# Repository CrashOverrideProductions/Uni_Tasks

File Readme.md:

# Bachelor of Cyber Security

<!-- Repo Stats -->

<!-- Languages Card ?-->

## Course overview
<p align="justify">
Deakin’s Bachelor of Cyber Security provides a solid foundation of the cyber security literacy and technical skills required by industry for a cyber security professional including those allowing you to be able to investigate and combat cyber-crime and cyber terrorism. The digital world is central to the way we live, work, communicate and conduct business. Now more than ever, it’s vital that the data and systems providing these services be safeguarded by ethical professionals with strong cyber security literacy and technical skills.
<br><br>
Whether it’s keeping in touch with friends on social networks, paying bills online, or using water or electricity, we depend on secure networked systems to keep our confidential information safe and rely on the assurance provided by custodians of this information to carry out activities in our day-to-day lives. Governments, military, financial institutions, hospitals and other businesses are all facing an unprecedented sophistication of cyber-attacks and there is a shortage of people with the skills and capability needed to ensure security in cyberspace.
<br><br>
This course will teach you how to identify, diagnose, analyse and manage the challenges of Cyber security. You’ll cover areas such as computer crime and digital forensics, evaluating software for security vulnerabilities, designing secure databases, securing operating systems, assessing and reinforcing the security of websites, integrating security requirements into new developments, designing secure network architectures, performing risk assessments and responding to cyber security incidents.
<br><br<>
Classes use specialised software to enable practice of real world cyber-attack and response scenarios. You’ll consequently get the chance to reflect on the need for cyber security in a working environment, and the various solutions that might apply. The degree focuses on technical elements and sets you up with strong skills in critical thinking and problem solving. You’ll be able to apply your learning in the workplace, and capably deal with imminent threats and challenges from the digital space where interconnected vehicles, drones, smart home gadgets, mobile and wearable devices, and health-kits prosper.
<br><br>
The course will help you develop strong interpersonal skills and a capacity for team-work. You’ll also build your written and oral communications skills, which means that you’ll graduate as a qualified and highly employable IT professional. Career options include work as a security analyst, project manager, security system manager, cryptographer, business analyst, consultant, security system developer or programmer, information security auditor, law enforcement personnel or IT security engineer. An honours year is available for high-achieving students upon completion of this degree.
<br><br>
As a graduate of this degree you’ll be eligible for professional recognition with the Australian Computer Society (ACS) – Australia’s leading professional association for the Information and Communication Technology (ICT) sector. As a member, you’ll receive international recognition for your skills as well as professional development opportunities, networking and information resources.Units in the course may include assessment hurdle requirements
</p>

---

## Course Progression
| Unit Code | Unit Name                                              | Type     | Status  | Mark       |
|:---------:|--------------------------------------------------------|---------:|:-------:|-----------:|
|  SIT124   | Exploring IT                                           | CORE     | &check; | RPL        |
|  SIT105   | Thinking Technology and Design                         | CORE     | &check; | RPL        |
|  SIT182   | Real World Practices for Cyber Security                | CORE     | &check; | PASS       |
|           | UNIT OF STUDY FROM A FIRST YEAR UNDERGRADUATE PROGRAM  | ELECTIVE | &check; | RPL        |
|  SIT103   | Data and Information Managment                         | CORE     | &check; | RPL        |
|  SIT102   | Introduction to Programming                            | CORE     | &check; | RPL        |
|  SIT123   | Data Capture Technologies                              | ELECTIVE | &check; | CREDIT     |
|           | UNIT OF STUDY FROM A FIRST YEAR UNDERGRADUATE PROGRAM  | ELECTIVE | &check; | RPL        |
|  SIT223   | Professional Practice in a Digital World               | CORE     | &cross; |            |
|  SIT192   | Discrete Mathmatics                                    | CORE     | &check; | PASS       |
|  SIT232   | Object Oriented Development                            | ELECTIVE | &check; | CREDIT     |
|           | UNIT OF STUDY FROM A SECOND YEAR UNDERGRADUATE PROGRAM | ELECTIVE | &check; | RPL        |
|  SIT210   | Networks and Communications                            | CORE     | &check; | PASS       |
|  SIT282   | Computer Crime and Digital Forensics                   | CORE     | &check; | PASS       |
|  SIT284   | Cyber Security Managment                               | CORE     | &check; | PASS       |
|  SIT281   | Cryptography                                           | CORE     | &cross; |            |
|  SIT384   | Data Analytics for Cyber Security                      | CORE     | &check; | DISTINCTION|
|  SIT379   | Ethical Hacking                                        | CORE     | &check; | CREDIT     |
|  SIT 374  | Project Design                                         | CORE     | &cross; |            |
|  SIT382   | System Security                                        | CORE     | &cross; |            |
|  SIT306   | IT Placement                                           | CORE     | &cross; |            |
|  SIT302   | Project Delivery                                       | CORE     | &cross; |            |
|  SIT210   | Embedded Systems Development                           | ELECTIVE | &check; | CREDIT     |
|           | Elective TBD                                           | ELECTIVE | &cross; |            |
|           |                                                        |          |         |            |
|           |                                                        |Total Completed |   | 17/24      |
---

## Course rules
To complete the Bachelor of Cyber Security, students must attain 24 credit points. Most units (think of units as ‘subjects’) are equal to 1 credit point. So that means in order to gain 24 credit points, you’ll need to study 24 units (AKA ‘subjects’) over your entire degree. Most students choose to study 4 units per trimester, and usually undertake two trimesters each year.

The course comprises a total of 24 credit points, which must include the following:
+ 17 core units 
+ 7 elective units
+ Completion of STP050 Academic Integrity (0-credit-point compulsory unit)
+ Completion of SIT010 Safety Induction Program (0-credit-point compulsory unit)
+ Completion of STP010 Introduction to Work Placements (0-credit-point compulsory unit) 
+ Level 1 – maximum of 10 credit points
+ Levels 2 and 3 – minimum of 14 credit points over both levels
+ Level 3 – minimum of 6 credit points of which at least 4 must be SIT Course Grouped unitsStudents are required to meet the University’s academic progress and conduct requirements. Visit Deakin’s website for more information

---

## Course Particulars
|||
|------------------------------------------------------:|---------------------------------------------------------------------------------------------------------|
| Year                                                  | 2018 course information                                                                                 |
| Award granted                                         | Bachelor of Cyber Security                                                                              |
| Course Map                                            | deakin.edu.au/students/enrolment-fees-and-money/enrolments/course-maps                                  | 
| Campus                                                | Offered at Burwood (Melbourne), Waurn Ponds (Geelong)                                                   |
| Cloud Campus                                          | Yes                                                                                                     |
| Duration                                              | 3 years full-time or part-time equivalent                                                               |
| CRICOS course code                                    | 091336M                                                                                                 |
| Deakin course code                                    | S334 (version 4)                                                                                        |
| Approval status                                       | This course is approved by the University under the Higher Education Standards Framework                | 
| Australian Qualifications Framework (AQF) recognition | The award conferred upon completion is recognised in the Australian Qualifications Framework at Level 7 |

---

## Licencing 
<p align="justify">
© Justin Bland & Deakin University; 2021
<br><br>
Except as permitted by the copyright law applicable to you, you may not reproduce or communicate any of the content on this website, including files downloadable from this website, without the permission of the copyright owner.
<br><br>
The Australian Copyright Act allows certain uses of content from the internet without the copyright owner’s permission. This includes uses by educational institutions and by Commonwealth and State governments, provided fair compensation is paid. For more information, see www.copyright.com.au and www.copyright.org.au.
<br><br>
The owners of copyright in the content on this website may receive compensation for the use of their content by educational institutions and governments, including from licensing schemes managed by Copyright Agency.
<br><br>
We may change these terms of use from time to time. Check before re-using any content from this website.
</p>

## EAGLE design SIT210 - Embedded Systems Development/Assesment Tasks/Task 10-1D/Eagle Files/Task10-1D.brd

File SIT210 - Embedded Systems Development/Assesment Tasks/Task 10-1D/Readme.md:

# SIT210 Task 10.1D  

### **Project**: Terrarium Thermostat 

<!-- Repo Cover Image -->

<!-- Repo Intro -->
### Task Objective
Objective of this task is to understand, trial, and design a Printed Circuit Board (PCB). PCBs are important components in prototyping and delivery of any electrical system.
For this task, you will need to design a PCB for your project (please note that you do not need to print the designs for this task, just the design). Your design should consider the following:
1. Your PCB does not need to include the SoC you are using (although some PCB design tools allow you to include chips like ATmega on your design). You can design your PC as a board to be used on the side, or as a shield/hat for your main device depending on which mark you are targeting (see below requirement for D/HD).
2. Your PCB should include all wiring, resistors, LEDs, sensors (either on the PCB itself, or with dedicated location/pins to soldier sensors on your PCB). If you are not designing a shield/hat, have interfaces for wiring from your main device to the PCB and clearly mark them on the PCB.

D: If you are targeting Distinction, your PCB could be in any form you wish. You can either make the board fit an enclosure/box of your liking.

~~HD: If you are targeting High Distinction, your PCB needs to take the form of a Shield for either a 40 pin Raspberry Pi (if using in your project, or designing PCB for 7.3D), or follow Feather standard (to be used with particle Argon.~~

#### Task Submission Details
You are required to submit two files for this task:
1. Create a Repository on Github and name it SIT210_PCB_Files and Put your design files/project on Github and a share the link to that repository on a document and submit on OnTrack
2. Provide a screenshot of the PCB you have developed.
Please note that unless you personally want that PCB, this task does not require your to have your design printed on an actual board.

---
<!-- Files -->
#### Files
|File     |Type|Link                                                                                                                                                                                                 | 
|---------|:--:|:---------------------------------------------------------------------------------------------------------------------------------------------------------------------------------------------------:|
|Schematic|.PDF|<a href="https://github.com/CrashOverrideProductions/ProfessionalDevelopment/blob/main/Uni%20Files/SIT210%20-%20Embedded%20Systems%20Development/Task%2010-1D/Schematic.pdf">This Directory</a>      |
|---------|----|------------------|
|Schematic|.SCH|<a href="https://github.com/CrashOverrideProductions/ProfessionalDevelopment/blob/main/Uni%20Files/SIT210%20-%20Embedded%20Systems%20Development/Task%2010-1D/Eagle%20Files/Task10-1D.sch">/Eagle</a>|
|Board    |.BRD|<a href="https://github.com/CrashOverrideProductions/ProfessionalDevelopment/blob/main/Uni%20Files/SIT210%20-%20Embedded%20Systems%20Development/Task%2010-1D/Eagle%20Files/Task10-1D.brd">/Eagle</a>|
|---------|----|------------------|
|Gerber   | N/A|<a href="https://github.com/CrashOverrideProductions/ProfessionalDevelopment/tree/main/Uni%20Files/SIT210%20-%20Embedded%20Systems%20Development/Task%2010-1D/Gerber">/Gerber</a>                    |
|---------|----|------------------|
|Renders  | N/A|<a href="https://github.com/CrashOverrideProductions/ProfessionalDevelopment/tree/main/Uni%20Files/SIT210%20-%20Embedded%20Systems%20Development/Task%2010-1D/Renders">/Renders</a>                  |

<!-- Licencing Always at the Bottom -->
---
### Licencing 

**Creative Commons: Attribution - NonCommercial - ShareAlike 4.0 International (CC BY-NC-SA 4.0)**

**You are free to:**
**Share** — copy and redistribute the material in any medium or format
**Adapt** — remix, transform, and build upon the material

**Under the following terms:**
**Attribution** — You must give appropriate credit, provide a link to the license, and indicate if changes were made. You may do so in any reasonable manner, but not in any way that suggests the licensor endorses you or your use.

**NonCommercial** — You may not use the material for commercial purposes.

**ShareAlike** — If you remix, transform, or build upon the material, you must distribute your contributions under the same license as the original.

No additional restrictions — You may not apply legal terms or technological measures that legally restrict others from doing anything the license permits.

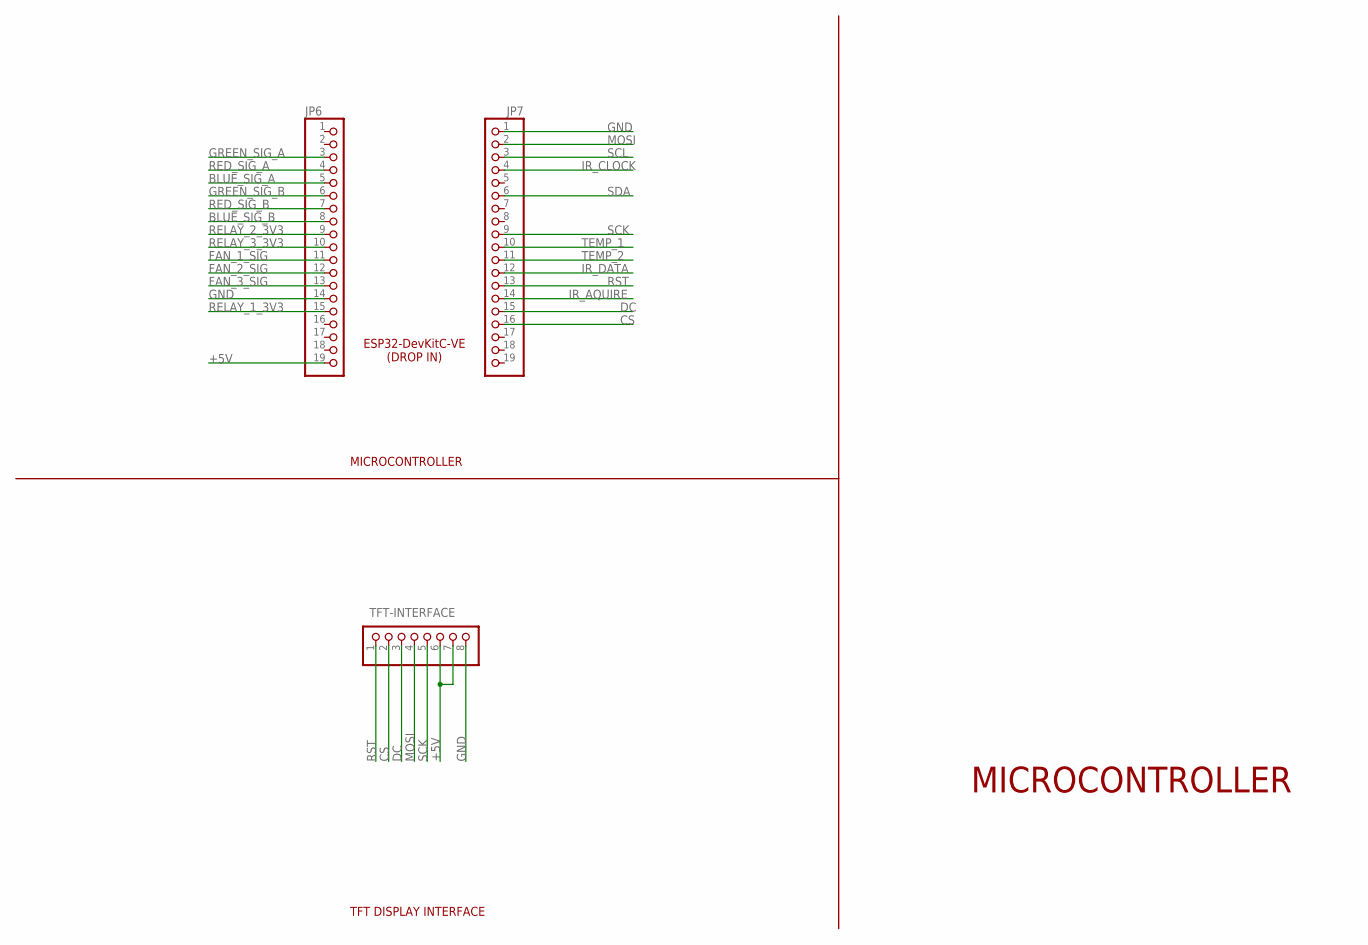
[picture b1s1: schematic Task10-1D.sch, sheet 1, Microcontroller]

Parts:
JP6, JP7: PINHD-1X19; 1X19
TFT-INTERFACE: PINHD-1X8; 1X08

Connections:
+5V: JP6.19, TFT-INTERFACE.6, TFT-INTERFACE.7; also elsewhere on the board
BLUE_SIG_A: JP6.5; also elsewhere on the board
BLUE_SIG_B: JP6.8; also elsewhere on the board
CS: JP7.16, TFT-INTERFACE.2
DC: JP7.15, TFT-INTERFACE.3
FAN_1_SIG: JP6.11; also elsewhere on the board
FAN_2_SIG: JP6.12; also elsewhere on the board
FAN_3_SIG: JP6.13; also elsewhere on the board
GND: JP6.14, JP7.1, TFT-INTERFACE.8; also elsewhere on the board
GREEN_SIG_A: JP6.3; also elsewhere on the board
GREEN_SIG_B: JP6.6; also elsewhere on the board
IR_AQUIRE: JP7.14; also elsewhere on the board
IR_CLOCK: JP7.4; also elsewhere on the board
IR_DATA: JP7.12; also elsewhere on the board
MOSI: JP7.2, TFT-INTERFACE.4
RED_SIG_A: JP6.4; also elsewhere on the board
RED_SIG_B: JP6.7; also elsewhere on the board
RELAY_1_3V3: JP6.15; also elsewhere on the board
RELAY_2_3V3: JP6.9; also elsewhere on the board
RELAY_3_3V3: JP6.10; also elsewhere on the board
RST: JP7.13, TFT-INTERFACE.1
SCK: JP7.9, TFT-INTERFACE.5
SCL: JP7.3; also elsewhere on the board
SDA: JP7.6; also elsewhere on the board
TEMP_1: JP7.10; also elsewhere on the board
TEMP_2: JP7.11; also elsewhere on the board

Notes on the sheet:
ESP32-DevKitC-VE (DROP IN)
MICROCONTROLLER
TFT DISPLAY INTERFACE

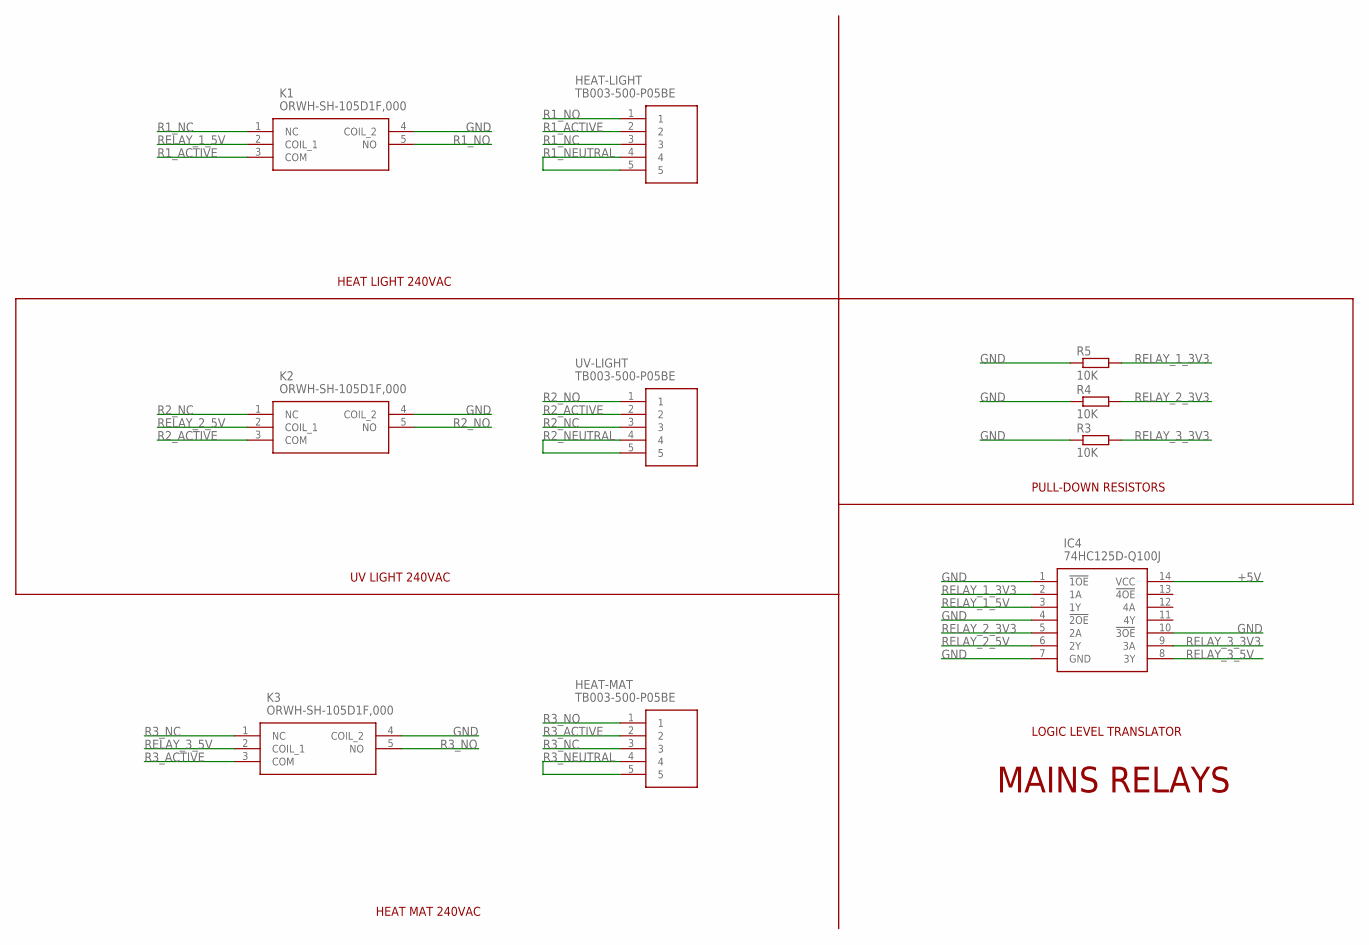
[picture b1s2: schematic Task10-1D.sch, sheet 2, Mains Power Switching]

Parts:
HEAT-LIGHT: TB003-500-P05BE; TB003500P05BE
HEAT-MAT: TB003-500-P05BE; TB003500P05BE
IC4: 74HC125D-Q100J; SOIC127P600X175-14N
K1, K2, K3: ORWH-SH-105D1F,000; ORWH-1T
R3, R4, R5: 10K; M0805
UV-LIGHT: TB003-500-P05BE; TB003500P05BE

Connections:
+5V: IC4.14 (VCC); also elsewhere on the board
GND: IC4.1 (!1OE), IC4.4 (!2OE), IC4.7 (GND), IC4.10 (!3OE), K1.4 (COIL_2), K2.4 (COIL_2), K3.4 (COIL_2), R3.1, R4.1, R5.1; also elsewhere on the board
R1_ACTIVE: HEAT-LIGHT.2, K1.3 (COM)
R1_NC: HEAT-LIGHT.3, K1.1 (NC)
R1_NEUTRAL: HEAT-LIGHT.4, HEAT-LIGHT.5
R1_NO: HEAT-LIGHT.1, K1.5 (NO)
R2_ACTIVE: K2.3 (COM), UV-LIGHT.2
R2_NC: K2.1 (NC), UV-LIGHT.3
R2_NEUTRAL: UV-LIGHT.4, UV-LIGHT.5
R2_NO: K2.5 (NO), UV-LIGHT.1
R3_ACTIVE: HEAT-MAT.2, K3.3 (COM)
R3_NC: HEAT-MAT.3, K3.1 (NC)
R3_NEUTRAL: HEAT-MAT.4, HEAT-MAT.5
R3_NO: HEAT-MAT.1, K3.5 (NO)
RELAY_1_3V3: IC4.2 (1A), R5.2; also elsewhere on the board
RELAY_1_5V: IC4.3 (1Y), K1.2 (COIL_1)
RELAY_2_3V3: IC4.5 (2A), R4.2; also elsewhere on the board
RELAY_2_5V: IC4.6 (2Y), K2.2 (COIL_1)
RELAY_3_3V3: IC4.9 (3A), R3.2; also elsewhere on the board
RELAY_3_5V: IC4.8 (3Y), K3.2 (COIL_1)

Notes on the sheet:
MAINS RELAYS
HEAT MAT 240VAC
UV LIGHT 240VAC
HEAT LIGHT 240VAC
LOGIC LEVEL TRANSLATOR
PULL-DOWN RESISTORS

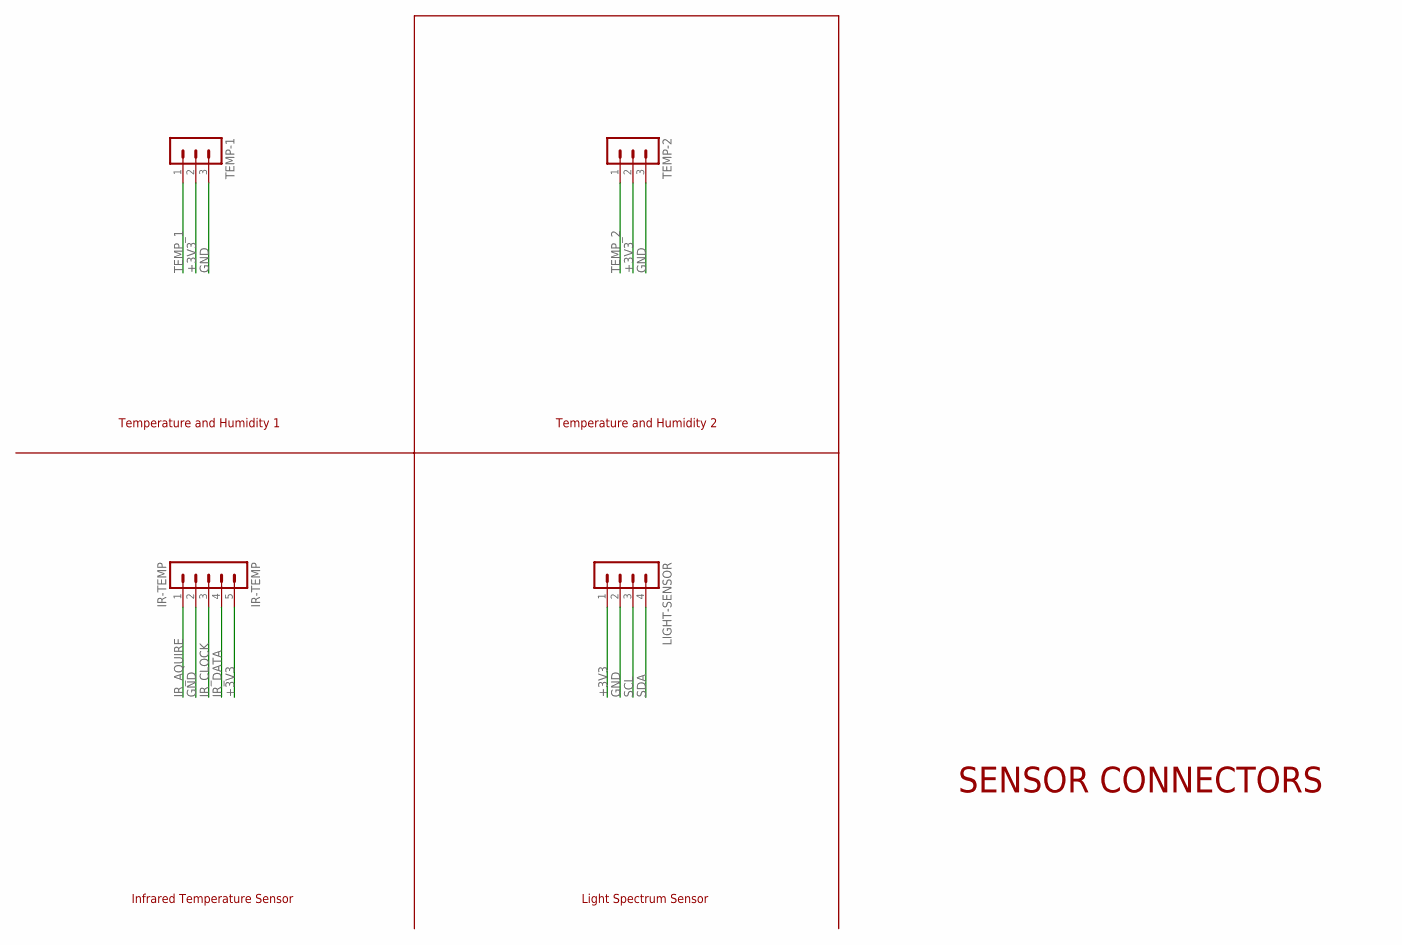
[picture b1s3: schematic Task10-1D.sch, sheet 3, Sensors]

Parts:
IR-TEMP: IR-TEMP; MA05-1
LIGHT-SENSOR: MA04-1
TEMP-1, TEMP-2: MA03-1

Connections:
+3V3: IR-TEMP.5, LIGHT-SENSOR.1, TEMP-1.2, TEMP-2.2; also elsewhere on the board
GND: IR-TEMP.2, LIGHT-SENSOR.2, TEMP-1.3, TEMP-2.3; also elsewhere on the board
IR_AQUIRE: IR-TEMP.1; also elsewhere on the board
IR_CLOCK: IR-TEMP.3; also elsewhere on the board
IR_DATA: IR-TEMP.4; also elsewhere on the board
SCL: LIGHT-SENSOR.3; also elsewhere on the board
SDA: LIGHT-SENSOR.4; also elsewhere on the board
TEMP_1: TEMP-1.1; also elsewhere on the board
TEMP_2: TEMP-2.1; also elsewhere on the board

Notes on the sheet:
Temperature and Humidity 1
Temperature and Humidity 2
Infrared Temperature Sensor
Light Spectrum Sensor
SENSOR CONNECTORS

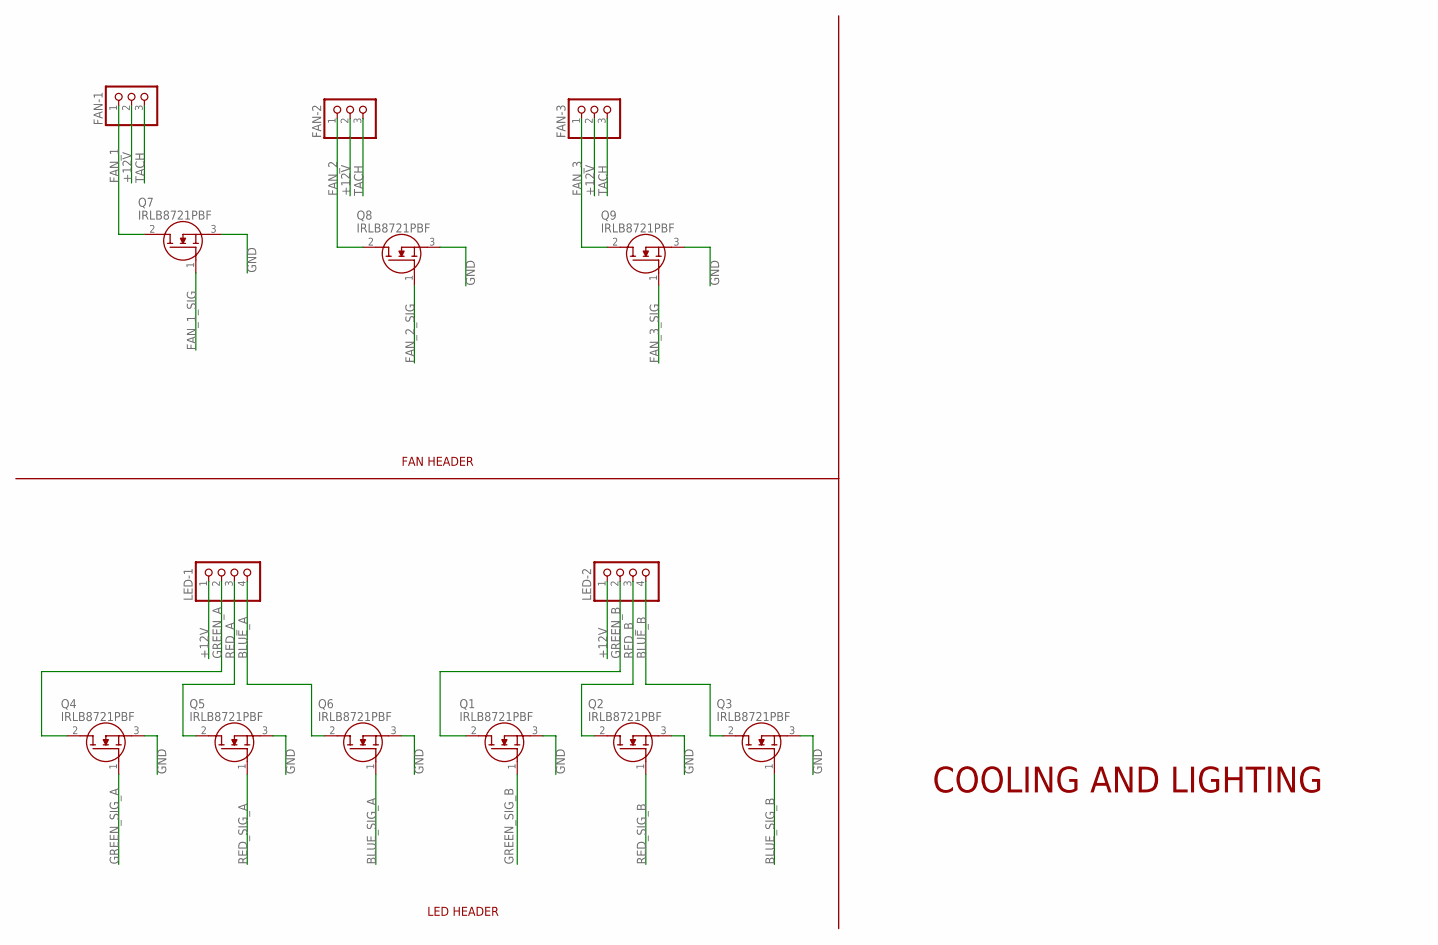
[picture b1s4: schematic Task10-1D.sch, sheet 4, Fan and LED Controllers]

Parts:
FAN-1, FAN-2, FAN-3: PINHD-1X3; 1X03
LED-1, LED-2: PINHD-1X4; 1X04
Q1, Q2, Q3, Q4, Q5, Q6, Q7, Q8, Q9: IRLB8721PBF; TO254P483X1016X1994-3P

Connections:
+12V: FAN-1.2, FAN-2.2, FAN-3.2, LED-1.1, LED-2.1; also elsewhere on the board
BLUE_A: LED-1.4, Q6.2 (D)
BLUE_B: LED-2.4, Q3.2 (D)
BLUE_SIG_A: Q6.1 (G); also elsewhere on the board
BLUE_SIG_B: Q3.1 (G); also elsewhere on the board
FAN_1: FAN-1.1, Q7.2 (D)
FAN_1_SIG: Q7.1 (G); also elsewhere on the board
FAN_2: FAN-2.1, Q8.2 (D)
FAN_2_SIG: Q8.1 (G); also elsewhere on the board
FAN_3: FAN-3.1, Q9.2 (D)
FAN_3_SIG: Q9.1 (G); also elsewhere on the board
GND: Q1.3 (S), Q2.3 (S), Q3.3 (S), Q4.3 (S), Q5.3 (S), Q6.3 (S), Q7.3 (S), Q8.3 (S), Q9.3 (S); also elsewhere on the board
GREEN_A: LED-1.2, Q4.2 (D)
GREEN_B: LED-2.2, Q1.2 (D)
GREEN_SIG_A: Q4.1 (G); also elsewhere on the board
GREEN_SIG_B: Q1.1 (G); also elsewhere on the board
RED_A: LED-1.3, Q5.2 (D)
RED_B: LED-2.3, Q2.2 (D)
RED_SIG_A: Q5.1 (G); also elsewhere on the board
RED_SIG_B: Q2.1 (G); also elsewhere on the board
TACH: FAN-1.3, FAN-2.3, FAN-3.3

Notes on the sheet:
LED HEADER
FAN HEADER
COOLING AND LIGHTING

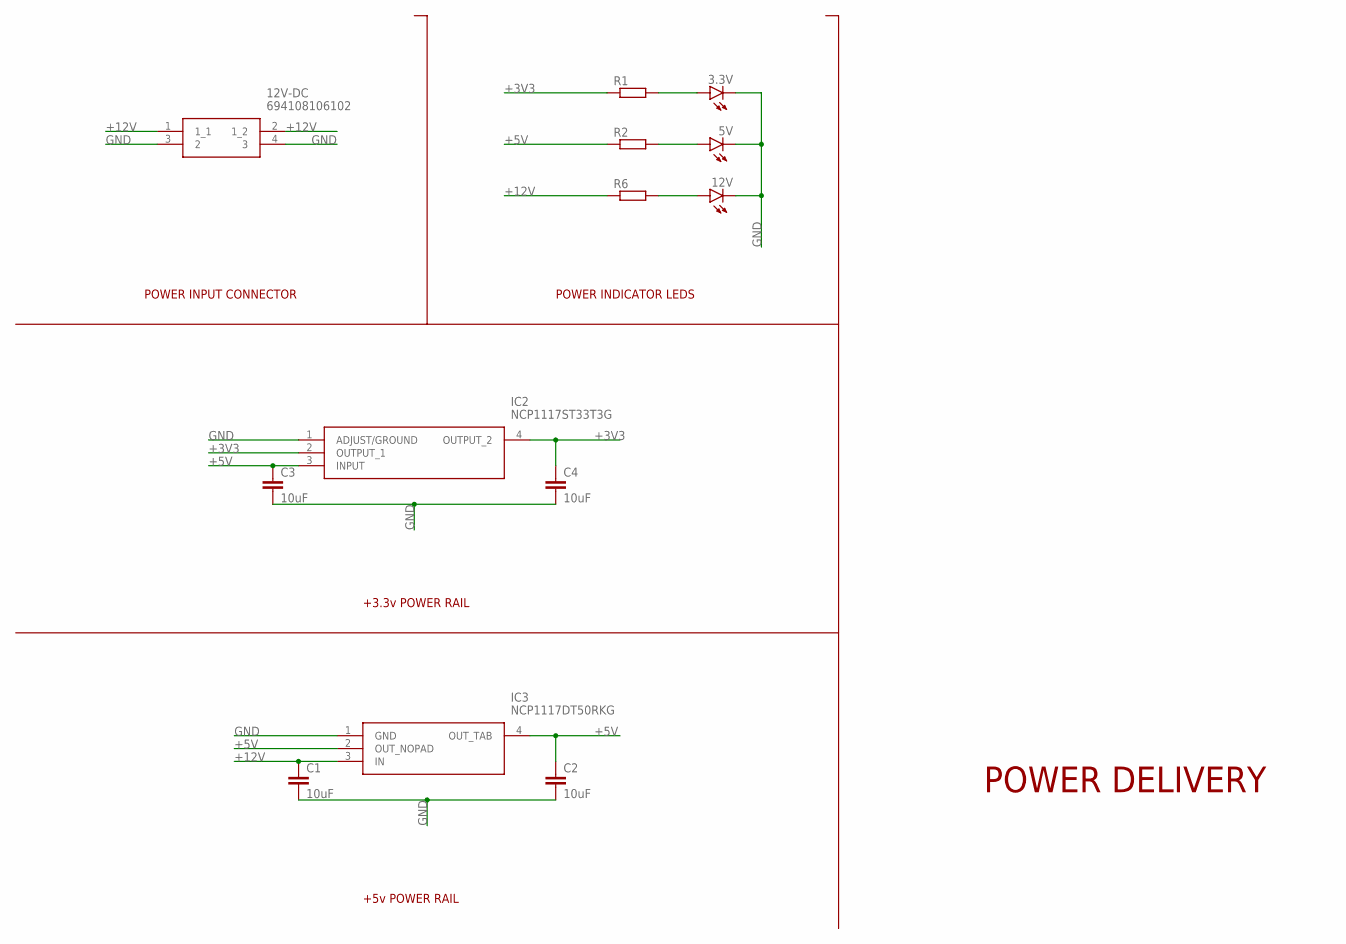
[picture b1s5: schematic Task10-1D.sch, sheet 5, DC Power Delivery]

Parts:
3.3V, 5V, 12V: LEDCHIP-LED0805; CHIP-LED0805
12V-DC: 694108106102
C1, C2, C3, C4: 10uF; C0805
IC2: NCP1117ST33T3G; SOT230P700X180-4N
IC3: NCP1117DT50RKG; TO229P990X238-4N
R1, R2, R6: R-EU_M0805; M0805

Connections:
+3V3: C4.1, IC2.2 (OUTPUT_1), IC2.4 (OUTPUT_2), R1.1; also elsewhere on the board
+5V: C2.1, C3.1, IC2.3 (INPUT), IC3.2 (OUT_NOPAD), IC3.4 (OUT_TAB), R2.1; also elsewhere on the board
+12V: 12V-DC.1 (1_1), 12V-DC.2 (1_2), C1.1, IC3.3 (IN), R6.1; also elsewhere on the board
GND: 3.3V.C, 5V.C, 12V.C, 12V-DC.3 (2), 12V-DC.4 (3), C1.2, C2.2, C3.2, C4.2, IC2.1 (ADJUST/GROUND), IC3.1 (GND); also elsewhere on the board
unnamed: 12V.A, R6.2
unnamed: 5V.A, R2.2
unnamed: 3.3V.A, R1.2

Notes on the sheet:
POWER INDICATOR LEDS
+5v POWER RAIL
+3.3v POWER RAIL
POWER INPUT CONNECTOR
POWER DELIVERY

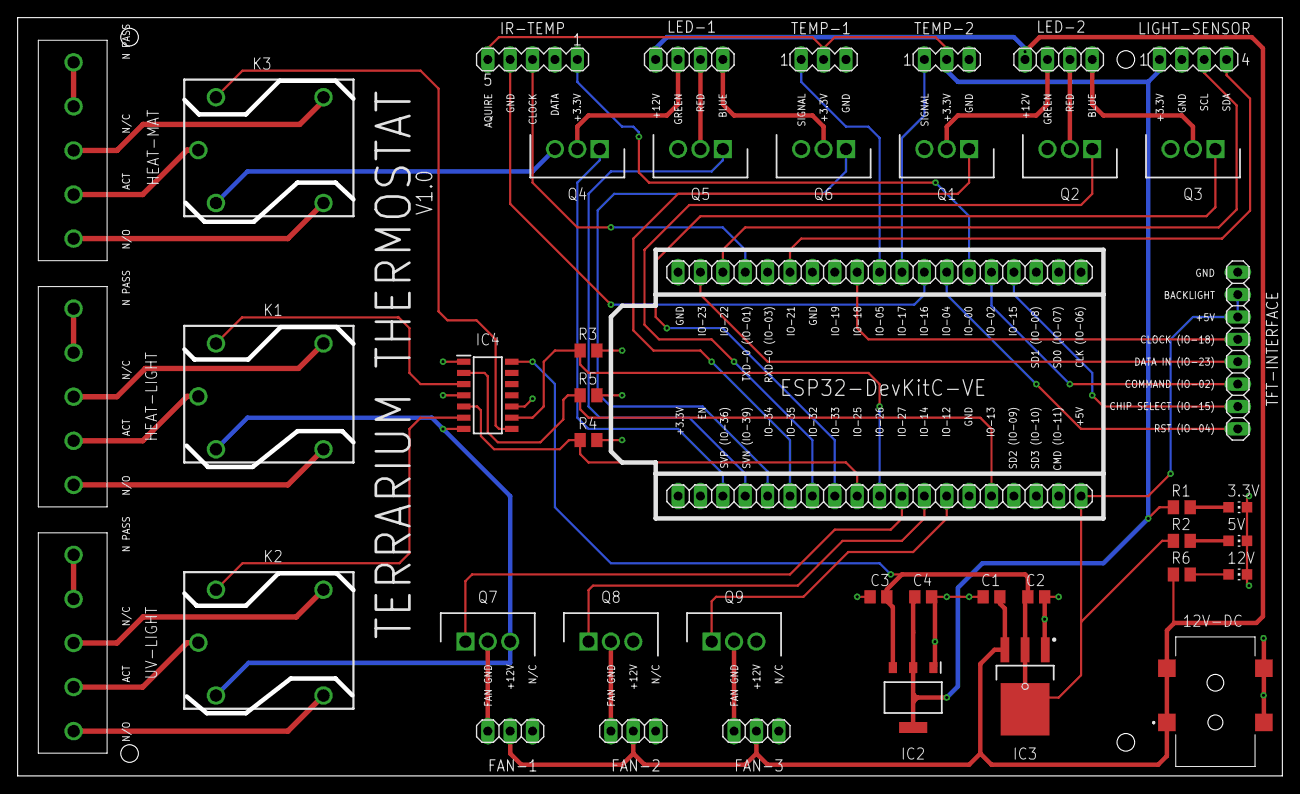
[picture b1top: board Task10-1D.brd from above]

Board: 2 copper layers, 143.5 x 86.0 mm, 44 parts (0 on the bottom side), 56 nets.

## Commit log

2021-06-26 repo upload

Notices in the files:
SIT210 - Embedded Systems Development/Assesment Tasks/Task 10-1D/Readme.md:
License: CC-BY-NC-SA-4.0
